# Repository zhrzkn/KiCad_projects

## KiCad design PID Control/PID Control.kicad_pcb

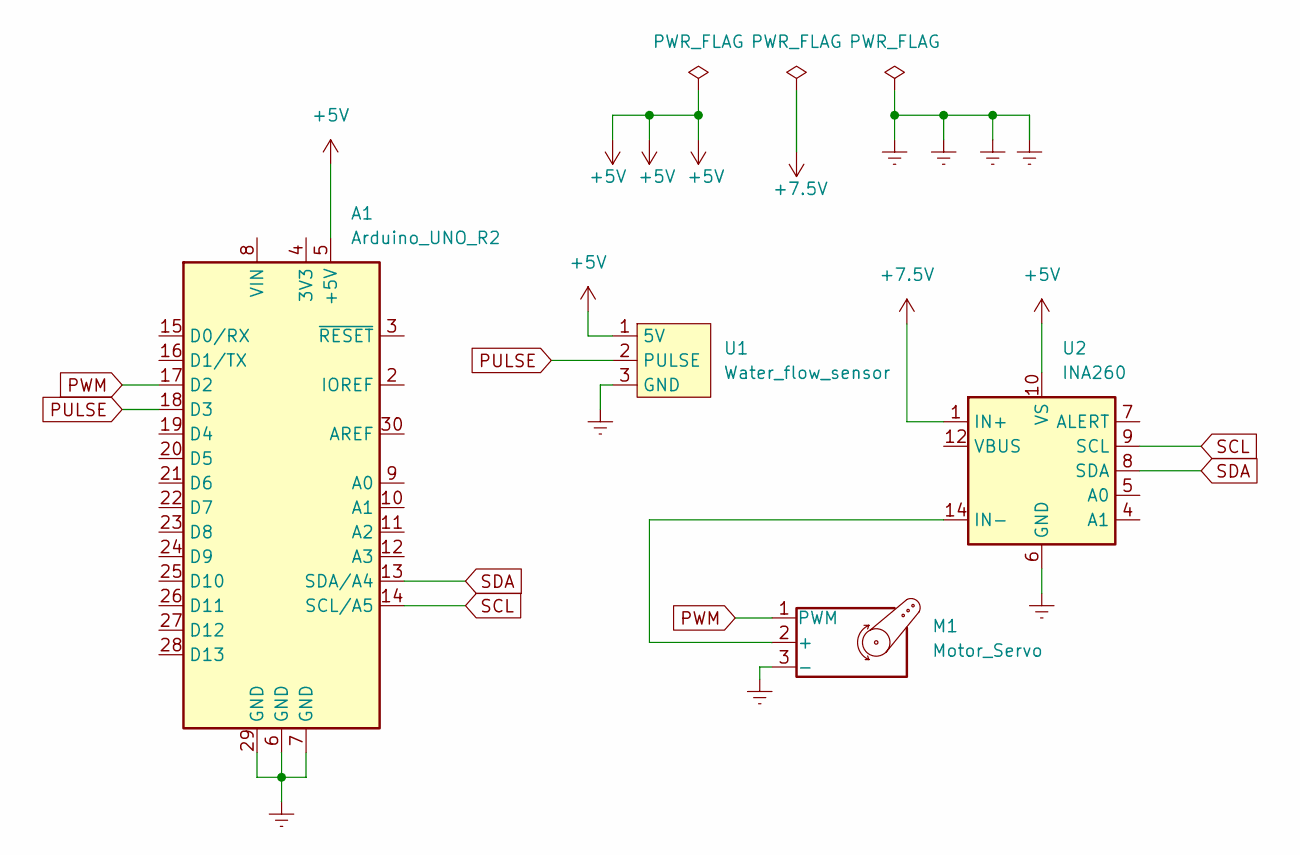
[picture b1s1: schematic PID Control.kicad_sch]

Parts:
A1: Arduino_UNO_R2
M1: Motor_Servo; Allegro_SIP-3
U1: Water_flow_sensor; Allegro_SIP-3
U2: INA260; TSSOP-16_4.4x5mm_P0.65mm

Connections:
+5V: A1.5 (+5V), U1.1 (5V), U2.10 (VS)
+7.5V: U2.1 (IN+), U2.2 (IN+), U2.3 (IN+)
Earth: A1.6 (GND), A1.7 (GND), A1.29 (GND), M1.3 (-), U1.3 (GND), U2.6 (GND), U2.11 (GND)
unnamed: M1.2 (+), U2.14 (IN-), U2.15 (IN-), U2.16 (IN-)
PULSE: A1.18 (D3), U1.2 (PULSE)
PWM: A1.17 (D2), M1.1 (PWM)
SCL: A1.14 (SCL/A5), U2.9 (SCL)
SDA: A1.13 (SDA/A4), U2.8 (SDA)

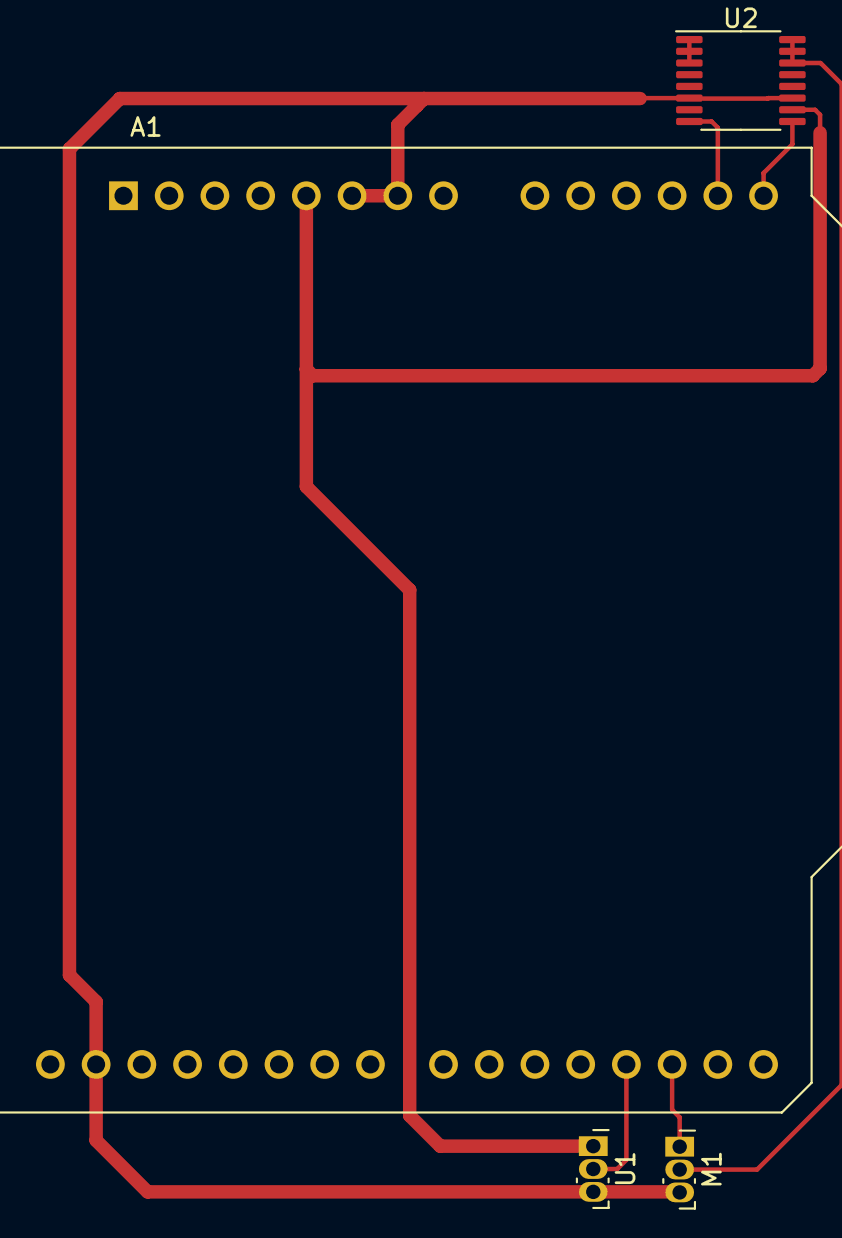
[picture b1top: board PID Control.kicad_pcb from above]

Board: 2 copper layers, 4 parts (0 on the bottom side), 8 nets.

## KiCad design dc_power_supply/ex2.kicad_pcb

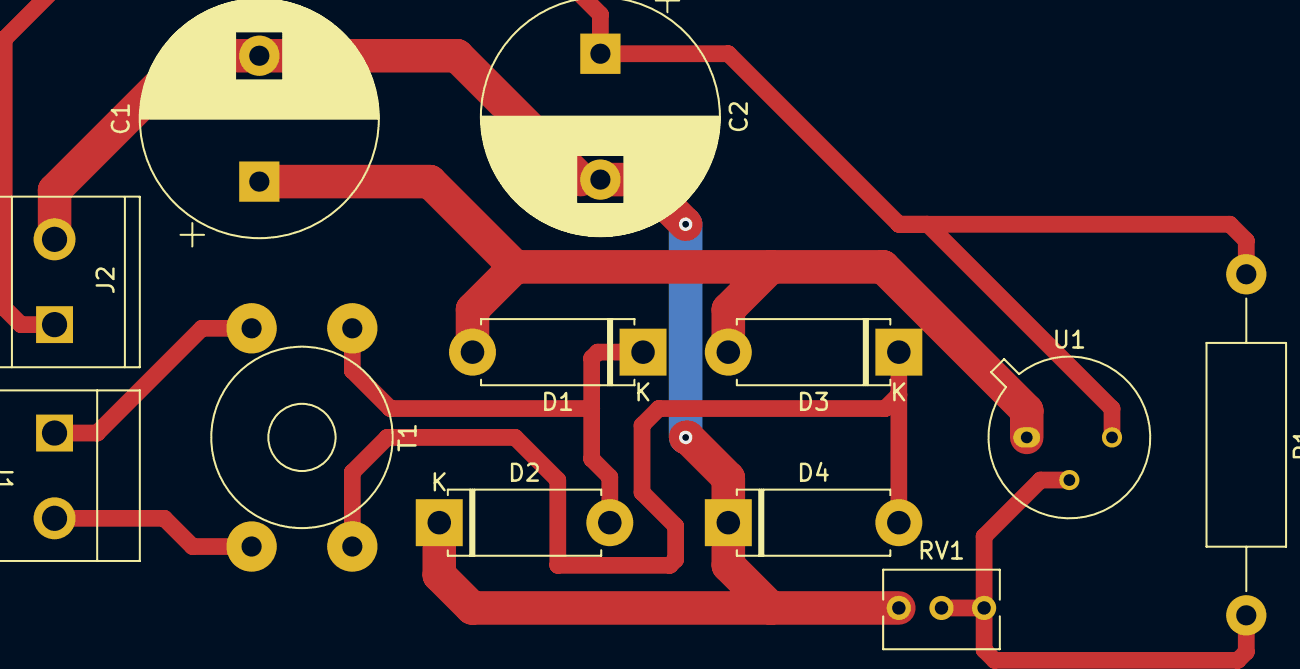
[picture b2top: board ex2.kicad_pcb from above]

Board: 2 copper layers, 12 parts (0 on the bottom side), 7 nets.

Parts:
C1: 220uF; CP_Radial_D14.0mm_P7.50mm
C2: 100uF; CP_Radial_D14.0mm_P7.50mm
D1, D2, D3, D4: DIODE; D_5W_P10.16mm_Horizontal
J1, J2: klemens; thermalblock
R1: 240R; R_Axial_DIN0414_L11.9mm_D4.5mm_P20.32mm_Horizontal
RV1: 3.6k; Potentiometer_Bourns_3266Y_Vertical
T1: Transformer_1P_1S; Transformer_Toroid_Horizontal_D10.5mm_Amidon-T37
U1: LM317_TO39; TO-39-3

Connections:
+12V: C1.1, D1.2 (A), D3.1 (K), D3.2 (A), D4.2 (A), T1.4 (SB), U1.1 (VI)
GND: C1.2, C2.2, D2.1 (K), D4.1 (K), J2.2 (gnd), RV1.3
unnamed: C2.1, J2.1 (vcc), R1.1, U1.3 (VO)
unnamed: D1.1 (K), D2.2 (A), T1.3 (SA)
unnamed: R1.2, RV1.1, RV1.2, U1.2 (ADJ)
unnamed: J1.1 (vcc), T1.1 (AA)
unnamed: J1.2 (gnd), T1.2 (AB)

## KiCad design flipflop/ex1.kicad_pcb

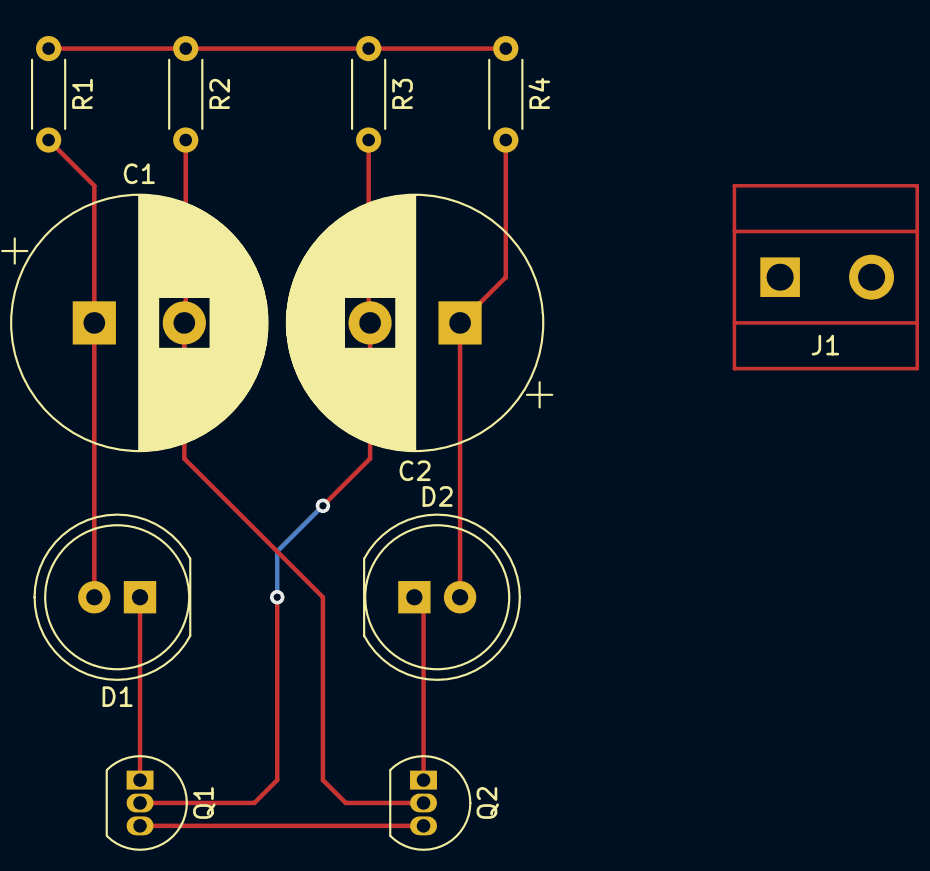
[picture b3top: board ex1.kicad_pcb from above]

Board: 2 copper layers, 11 parts (0 on the bottom side), 8 nets.

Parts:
C1, C2: 100uF; CP_Radial_D14.0mm_P5.00mm
D1, D2: LED; LED_D8.0mm
J1: termalblock; thermalblock
Q1, Q2: BC237; TO-92_Inline
R1, R3: 470R; R_Axial_DIN0204_L3.6mm_D1.6mm_P5.08mm_Horizontal
R2, R4: 10K; R_Axial_DIN0204_L3.6mm_D1.6mm_P5.08mm_Horizontal

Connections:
GND: Q1.3 (E), Q2.3 (E)
unnamed: C1.1, D1.2 (A), R1.2
unnamed: C1.2, Q2.2 (B), R2.2
unnamed: C2.1, D2.2 (A), R4.2
unnamed: C2.2, Q1.2 (B), R3.2
unnamed: D1.1 (K), Q1.1 (C)
unnamed: D2.1 (K), Q2.1 (C)
VCC: R1.1, R2.1, R3.1, R4.1

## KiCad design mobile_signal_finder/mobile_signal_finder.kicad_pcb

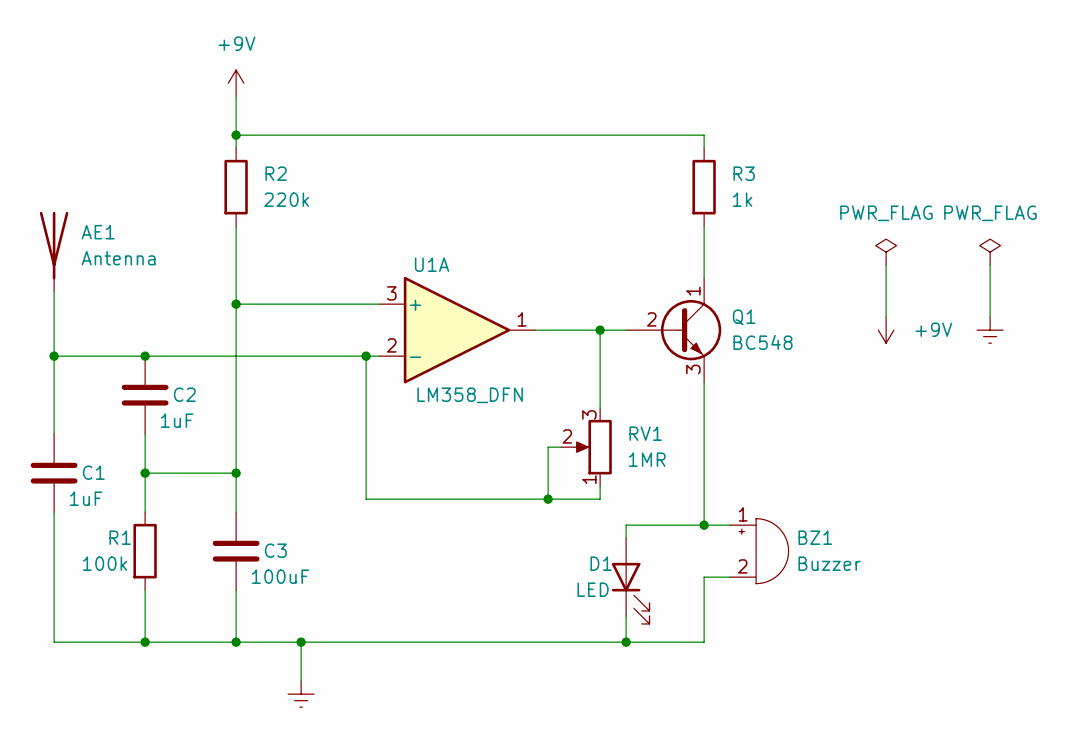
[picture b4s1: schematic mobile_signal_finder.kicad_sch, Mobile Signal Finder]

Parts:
AE1: Antenna; Texas_SWRA117D_2.4GHz_Left
BZ1: Buzzer; MagneticBuzzer_CUI_CST-931RP-A
C1, C2: 1uF; C_0805_2012Metric
C3: 100uF; C_0805_2012Metric
D1: LED; LED_D3.0mm
Q1: BC548; TO-92_Inline
R1: 100k; R_0805_2012Metric
R2: 220k; R_0805_2012Metric
R3: 1k; R_0805_2012Metric
RV1: 1MR; Potentiometer_Bourns_3009Y_Horizontal
U1: LM358_DFN; DFN-8-1EP_2x2mm_P0.5mm_EP1.05x1.75mm

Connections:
+9V: R2.1, R3.1
Earth: BZ1.2 (+), C1.2, C3.2, D1.1 (K), R1.2
unnamed: AE1.1 (A), C1.1, C2.1, RV1.1, RV1.2, U1.2 (-)
unnamed: BZ1.1 (-), D1.2 (A), Q1.3 (E)
unnamed: C2.2, C3.1, R1.1, R2.2, U1.3 (+)
unnamed: Q1.1 (C), R3.2
unnamed: Q1.2 (B), RV1.3, U1.1

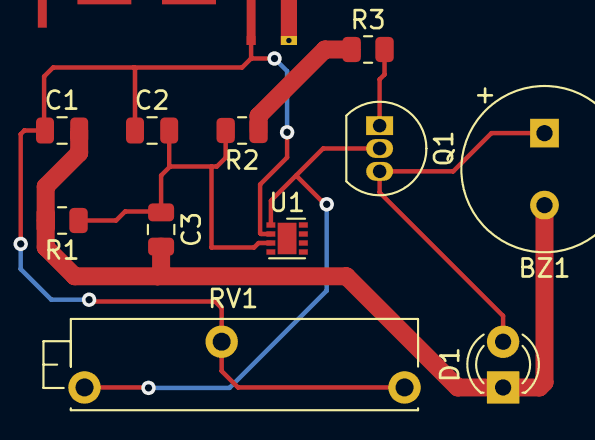
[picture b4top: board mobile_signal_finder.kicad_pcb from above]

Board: 2 copper layers, 12 parts (0 on the bottom side), 7 nets.

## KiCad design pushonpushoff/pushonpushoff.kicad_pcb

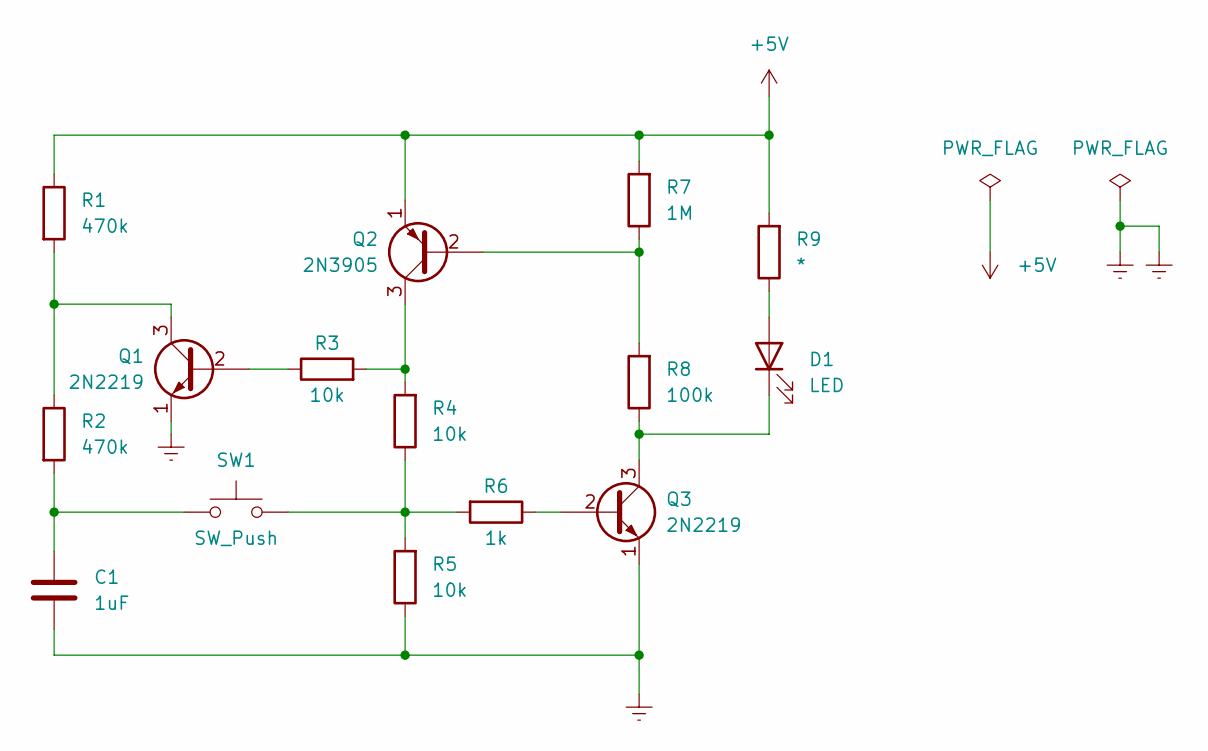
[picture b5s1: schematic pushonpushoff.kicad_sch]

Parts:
C1: 1uF; C_0805_2012Metric
D1: LED; LED_D4.0mm
Q1, Q3: 2N2219; TO-39-3
Q2: 2N3905; TO-92_Inline
R1, R2: 470k; R_1206_3216Metric
R3, R4, R5: 10k; R_1206_3216Metric
R6: 1k; R_1206_3216Metric
R7: 1M; R_1206_3216Metric
R8: 100k; R_1206_3216Metric
R9: *; R_1206_3216Metric
SW1: SW_Push; SW_Matias_1.50u

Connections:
+5V: Q2.1 (E), R1.1, R7.2, R9.2
Earth: C1.2, Q1.1 (E), Q3.1 (E), R5.1
unnamed: C1.1, R2.2, SW1.1
unnamed: D1.1 (K), Q3.3 (C), R8.1
unnamed: D1.2 (A), R9.1
unnamed: Q1.2 (B), R3.1
unnamed: Q1.3 (C), R1.2, R2.1
unnamed: Q2.2 (B), R7.1, R8.2
unnamed: Q2.3 (C), R3.2, R4.2
unnamed: Q3.2 (B), R6.1
unnamed: R4.1, R5.2, R6.2, SW1.2

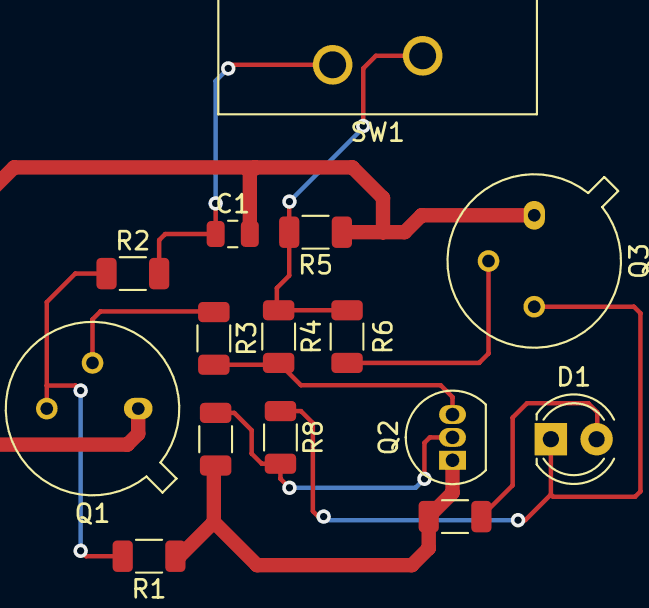
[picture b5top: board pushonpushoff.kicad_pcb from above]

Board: 2 copper layers, 15 parts (0 on the bottom side), 11 nets.

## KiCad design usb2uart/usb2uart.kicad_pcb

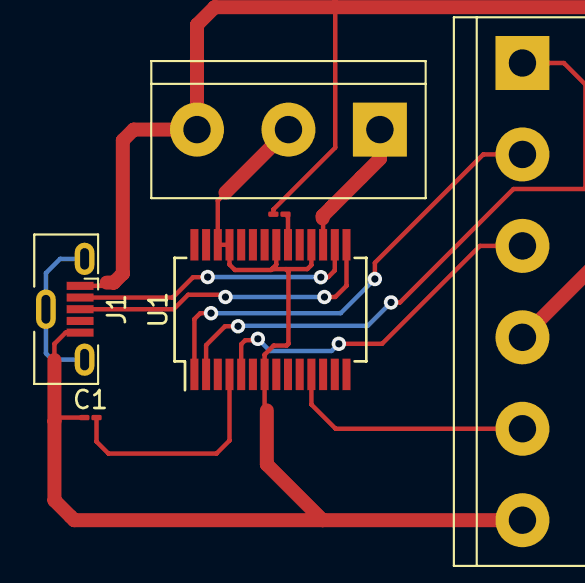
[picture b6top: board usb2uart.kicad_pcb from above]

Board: 2 copper layers, 6 parts (0 on the bottom side), 11 nets.

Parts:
C1: 1uF; C_01005_0402Metric_Pad0.57x0.30mm_HandSolder
CV: 100nF; C_01005_0402Metric_Pad0.57x0.30mm_HandSolder
J1: USB_B_Micro; USB_Micro-B_Molex-105133-0001
U1: FT232RL; SSOP-28_5.3x10.2mm_P0.65mm
U2: 3_jumper; TerminalBlock_bornier-3_P5.08mm
U3: 6_jumper; TerminalBlock_bornier-6_P5.08mm

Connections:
+3V3: U1.17 (3V3OUT), U2.1 (+3V3)
+5V: CV.1, J1.1 (VBUS), U2.3 (5V), U3.4 (VCC)
/CTS: U1.11 (CTS), U3.5 (CTS)
/DTR: U1.2 (DTR), U3.1 (DTR)
/RXD0: U1.1 (TXD), U3.2 (RX)
/TXD0: U1.5 (RXD), U3.3 (TX)
Earth: C1.1, J1.5 (GND), U1.7 (GND), U1.18 (GND), U1.21 (GND), U1.25 (AGND), U1.26 (TEST), U2.2 (GND), U3.6 (GND)
unnamed: C1.2, U1.4 (VCCIO)
unnamed: CV.2, U1.20 (VCC)
unnamed: J1.2 (D-), U1.16 (USBD-)
unnamed: J1.3 (D+), U1.15 (USBD+)

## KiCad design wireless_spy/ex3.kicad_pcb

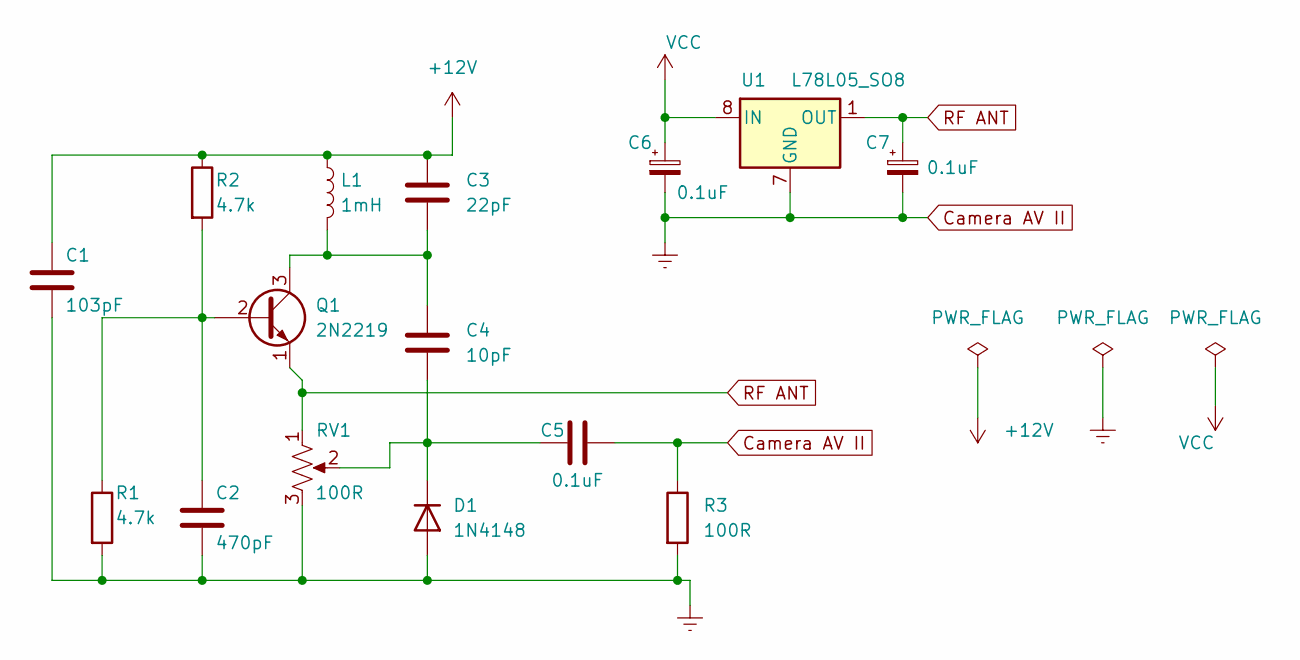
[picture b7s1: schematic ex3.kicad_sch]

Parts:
C1: 103pF; CP_Elec_3x5.3
C2: 470pF; CP_Elec_3x5.3
C3: 22pF; CP_Elec_3x5.3
C4: 10pF; CP_Elec_3x5.3
C5, C6, C7: 0.1uF; CP_Elec_3x5.3
D1: 1N4148; D_DO-35_SOD27_P7.62mm_Horizontal
L1: 1mH; L_6.3x6.3_H3
Q1: 2N2219; TO-39-3
R1, R2: 4.7k; R_0805_2012Metric
R3: 100R; R_0805_2012Metric
RV1: 100R; Potentiometer_Bourns_3214G_Horizontal
U1: L78L05_SO8; SOIC-8_3.9x4.9mm_P1.27mm

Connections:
+12V: C1.1, C3.1, L1.1, R2.1
Camera AV II: C1.2, C2.2, C5.2, C6.2, C7.2, D1.2 (A), R1.2, R3.1, R3.2, RV1.3, U1.2 (GND), U1.3 (GND), U1.6 (GND), U1.7 (GND)
unnamed: C2.1, Q1.2 (B), R1.1, R2.2
unnamed: C3.2, C4.1, L1.2, Q1.3 (C)
unnamed: C4.2, C5.1, D1.1 (K), RV1.2
RF ANT: C7.1, Q1.1 (E), RV1.1, U1.1 (OUT)
VCC: C6.1, U1.8 (IN)

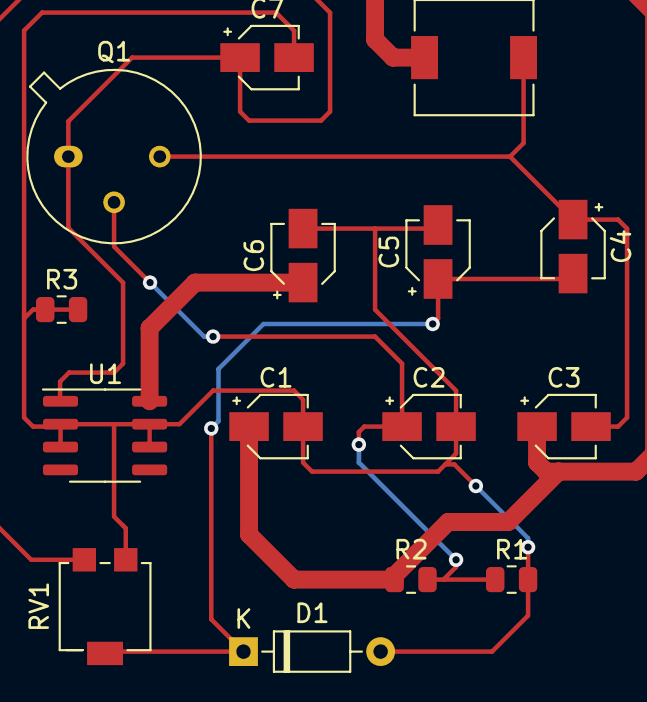
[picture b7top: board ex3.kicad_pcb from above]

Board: 2 copper layers, 15 parts (0 on the bottom side), 7 nets.
